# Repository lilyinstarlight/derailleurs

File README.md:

The Derailleurs
===============

The Derailleurs aim to create a system for automatic rear gear switching on a standard bicycle. This repository contains everything we've made toward that goal.

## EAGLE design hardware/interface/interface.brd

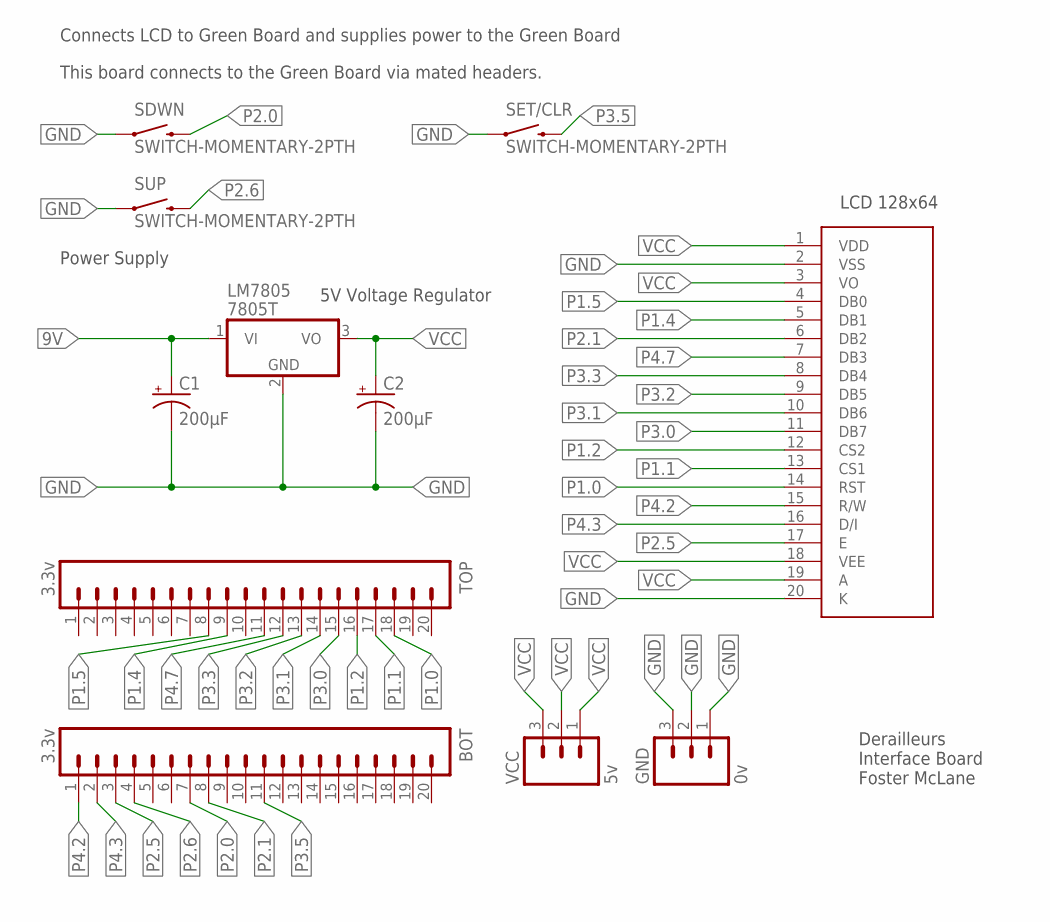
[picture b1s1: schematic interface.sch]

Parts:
BOT: 3.3v; 1X20
C1, C2: 200µF; CPOL-RADIAL-100UF-25V
GND: 0v; 1X03
LM7805: 7805T; TO220H
SDWN: SWITCH-MOMENTARY-2PTH; TACTILE-PTH
SET/CLR: SWITCH-MOMENTARY-2PTH; TACTILE-PTH
SUP: SWITCH-MOMENTARY-2PTH; TACTILE-PTH
TOP: 3.3v; 1X20
U$1: LCD-G12864FULL; LCD-G12864
VCC: 5v; 1X03

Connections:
9V: C1.1 (+), LM7805.1 (VI)
GND: C1.2 (-), C2.2 (-), GND.1, GND.2, GND.3, LM7805.2 (GND), SDWN.1, SET/CLR.1, SUP.1, U$1.2 (VSS), U$1.20 (K)
P1.0: TOP.18, U$1.14 (RST)
P1.1: TOP.17, U$1.13 (CS1)
P1.2: TOP.16, U$1.12 (CS2)
P1.4: TOP.9, U$1.5 (DB1)
P1.5: TOP.8, U$1.4 (DB0)
P2.0: BOT.7, SDWN.3 (2)
P2.1: BOT.8, U$1.6 (DB2)
P2.5: BOT.3, U$1.17 (E)
P2.6: BOT.4, SUP.3 (2)
P3.0: TOP.15, U$1.11 (DB7)
P3.1: TOP.14, U$1.10 (DB6)
P3.2: TOP.13, U$1.9 (DB5)
P3.3: TOP.12, U$1.8 (DB4)
P3.5: BOT.11, SET/CLR.3 (2)
P4.2: BOT.1, U$1.15 (R/W)
P4.3: BOT.2, U$1.16 (D/I)
P4.7: TOP.11, U$1.7 (DB3)
VCC: C2.1 (+), LM7805.3 (VO), U$1.1 (VDD), U$1.3 (VO), U$1.18 (VEE), U$1.19 (A), VCC.1, VCC.2, VCC.3

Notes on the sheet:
LCD 128x64
5V Voltage Regulator
Power Supply
Connects LCD to Green Board and supplies power to the Green Board
This board connects to the Green Board via mated headers.
Derailleurs Interface Board Foster McLane

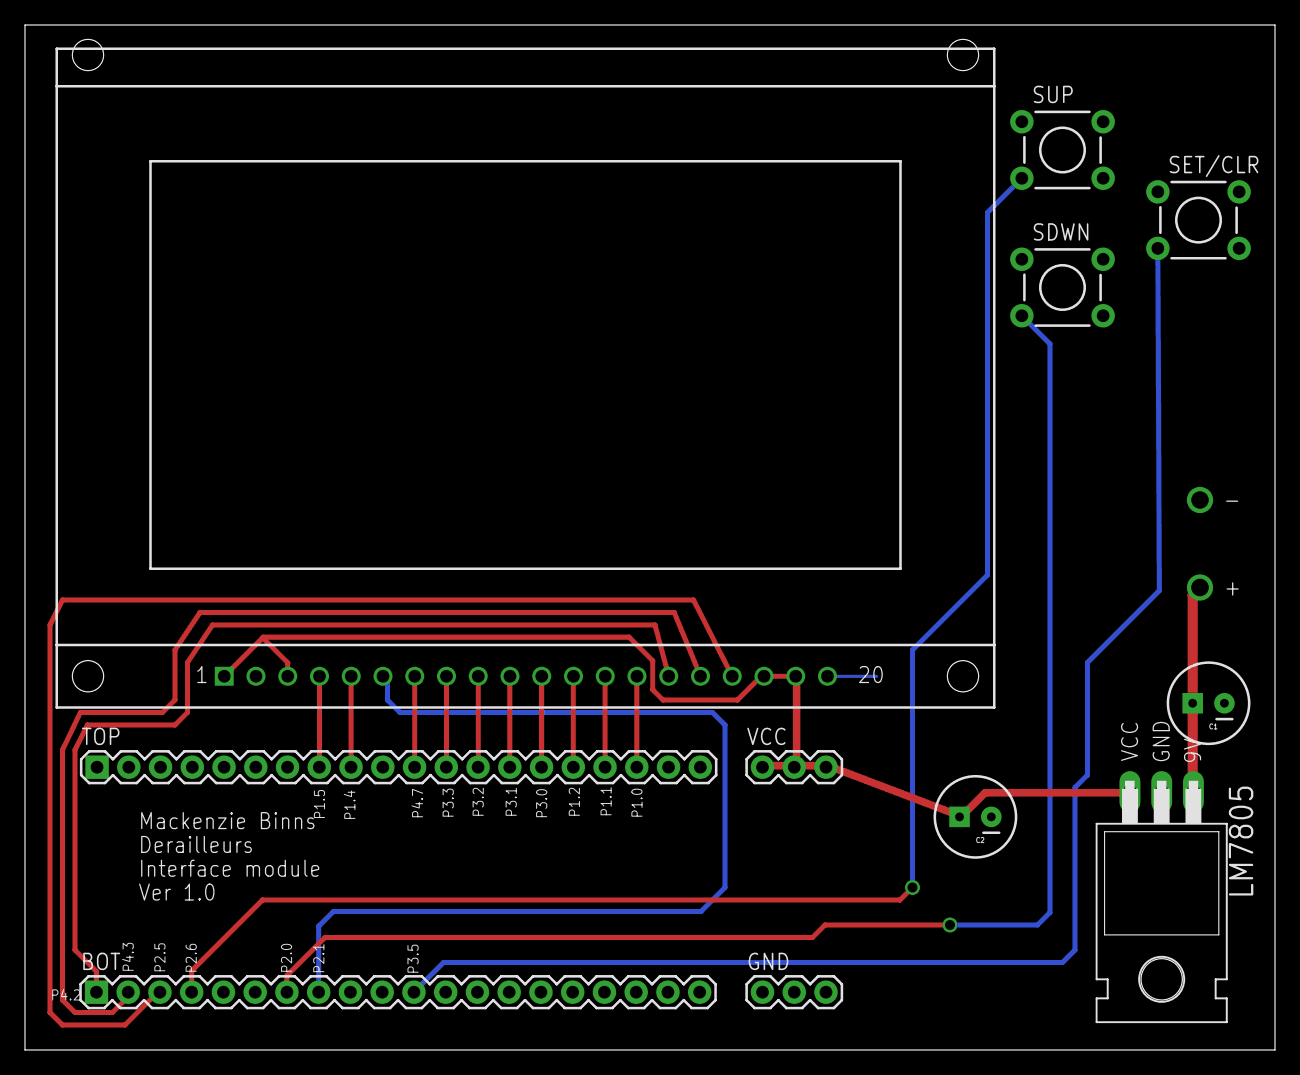
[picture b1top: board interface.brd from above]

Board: 2 copper layers, 100.0 x 82.0 mm, 11 parts (0 on the bottom side), 20 nets.

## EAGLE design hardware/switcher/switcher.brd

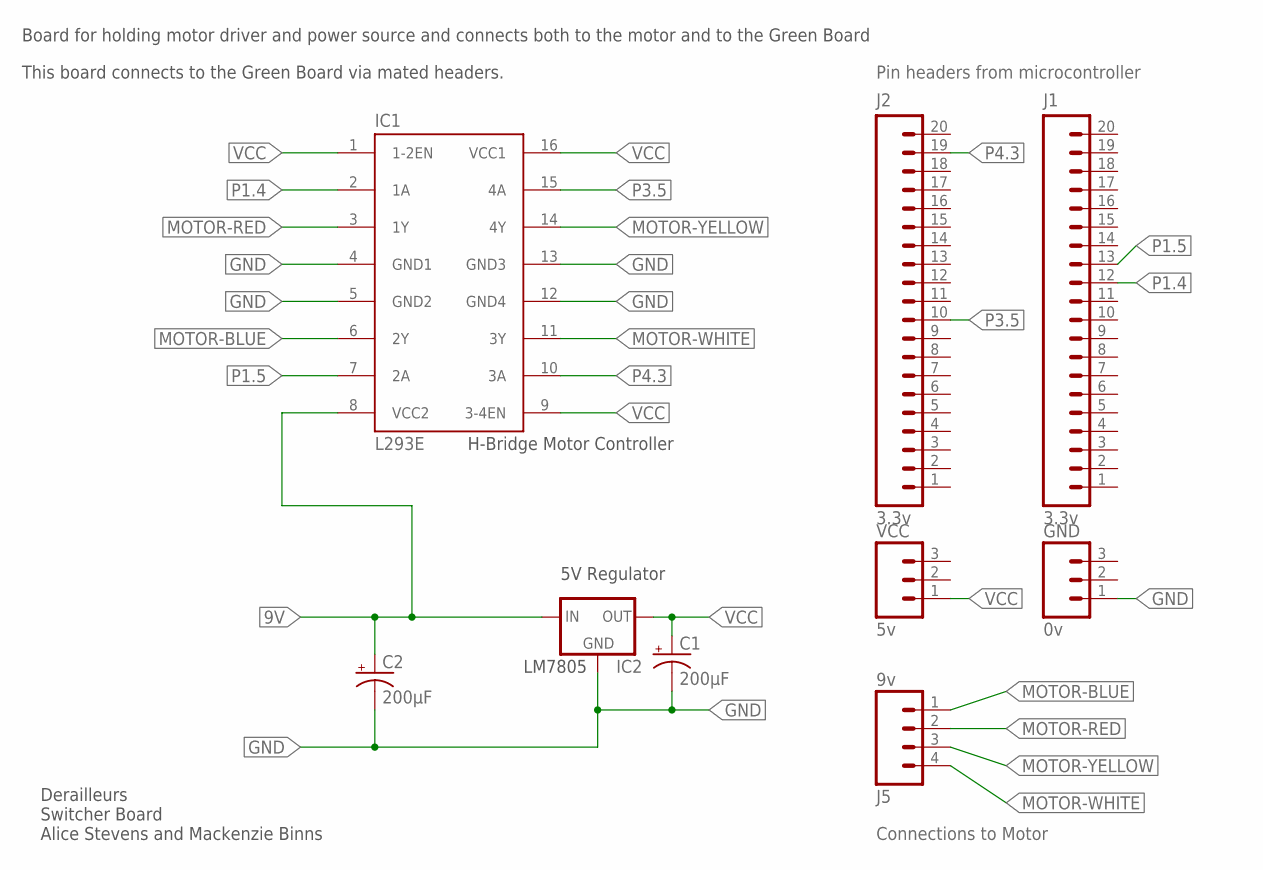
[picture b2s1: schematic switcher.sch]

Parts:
C1, C2: 200µF; CPOL-RADIAL-100UF-25V
GND: 0v; 1X03
IC1: L293E; DIL16
IC2: 78XXL
J1, J2: 3.3v; 1X20
J5: 9v; 1X04
VCC: 5v; 1X03

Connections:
9V: C2.1 (+), IC1.8 (VCC2), IC2.IN
GND: C1.2 (-), C2.2 (-), GND.1, IC1.4 (GND1), IC1.5 (GND2), IC1.12 (GND4), IC1.13 (GND3), IC2.GND
MOTOR-BLUE: IC1.6 (2Y), J5.1
MOTOR-RED: IC1.3 (1Y), J5.2
MOTOR-WHITE: IC1.11 (3Y), J5.4
MOTOR-YELLOW: IC1.14 (4Y), J5.3
P1.4: IC1.2 (1A), J1.12
P1.5: IC1.7 (2A), J1.13
P3.5: IC1.15 (4A), J2.10
P4.3: IC1.10 (3A), J2.19
VCC: C1.1 (+), IC1.1 (1-2EN), IC1.9 (3-4EN), IC1.16 (VCC1), IC2.OUT, VCC.1

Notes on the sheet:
Board for holding motor driver and power source and connects both to the motor and to the Green Board
H-Bridge Motor Controller
LM7805
5V Regulator
This board connects to the Green Board via mated headers.
Derailleurs Switcher Board Alice Stevens and Mackenzie Binns
Pin headers from microcontroller
Connections to Motor

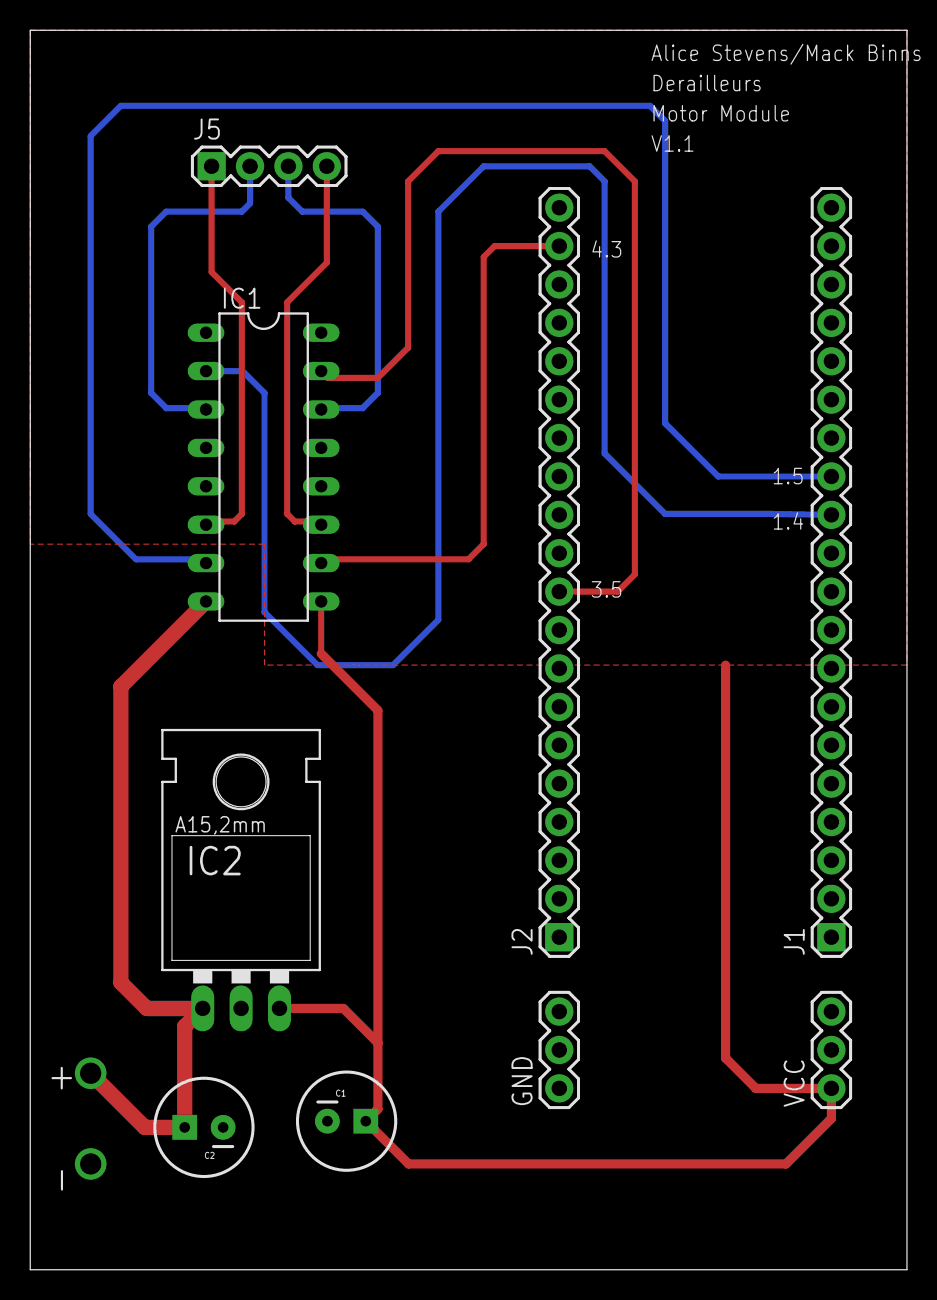
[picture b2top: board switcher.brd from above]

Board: 2 copper layers, 58.0 x 82.0 mm, 9 parts (0 on the bottom side), 11 nets.

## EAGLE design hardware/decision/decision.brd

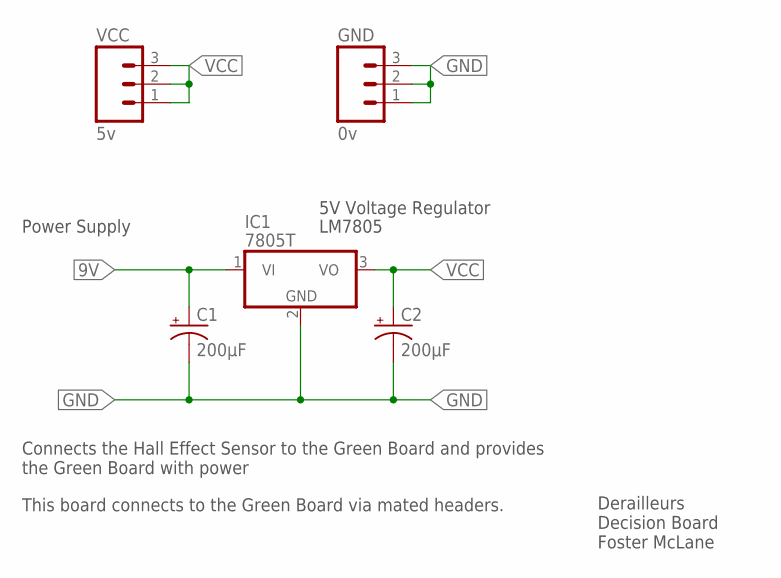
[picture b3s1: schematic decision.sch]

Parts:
C1, C2: 200µF; CPOL-RADIAL-100UF-25V
GND: 0v; 1X03
IC1: 7805T; TO220H
VCC: 5v; 1X03

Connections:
9V: C1.1 (+), IC1.1 (VI)
GND: C1.2 (-), C2.2 (-), GND.1, GND.2, GND.3, IC1.2 (GND)
VCC: C2.1 (+), IC1.3 (VO), VCC.1, VCC.2, VCC.3

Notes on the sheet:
LM7805
5V Voltage Regulator
Connects the Hall Effect Sensor to the Green Board and provides the Green Board with power
This board connects to the Green Board via mated headers.
Derailleurs Decision Board Foster McLane
Power Supply

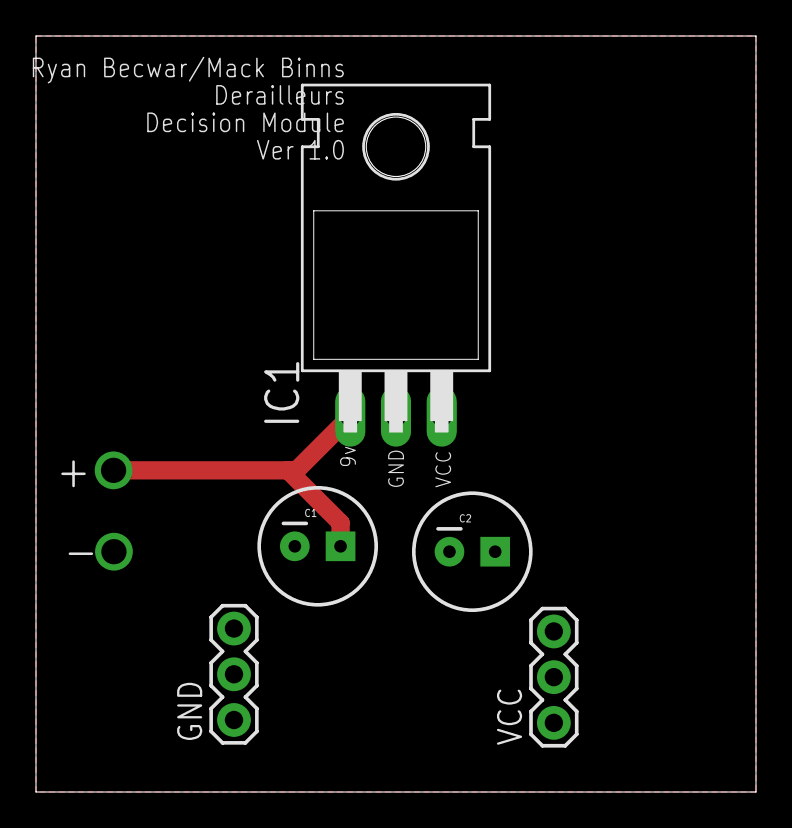
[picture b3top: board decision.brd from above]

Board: 2 copper layers, 40.0 x 42.0 mm, 5 parts (0 on the bottom side), 3 nets.

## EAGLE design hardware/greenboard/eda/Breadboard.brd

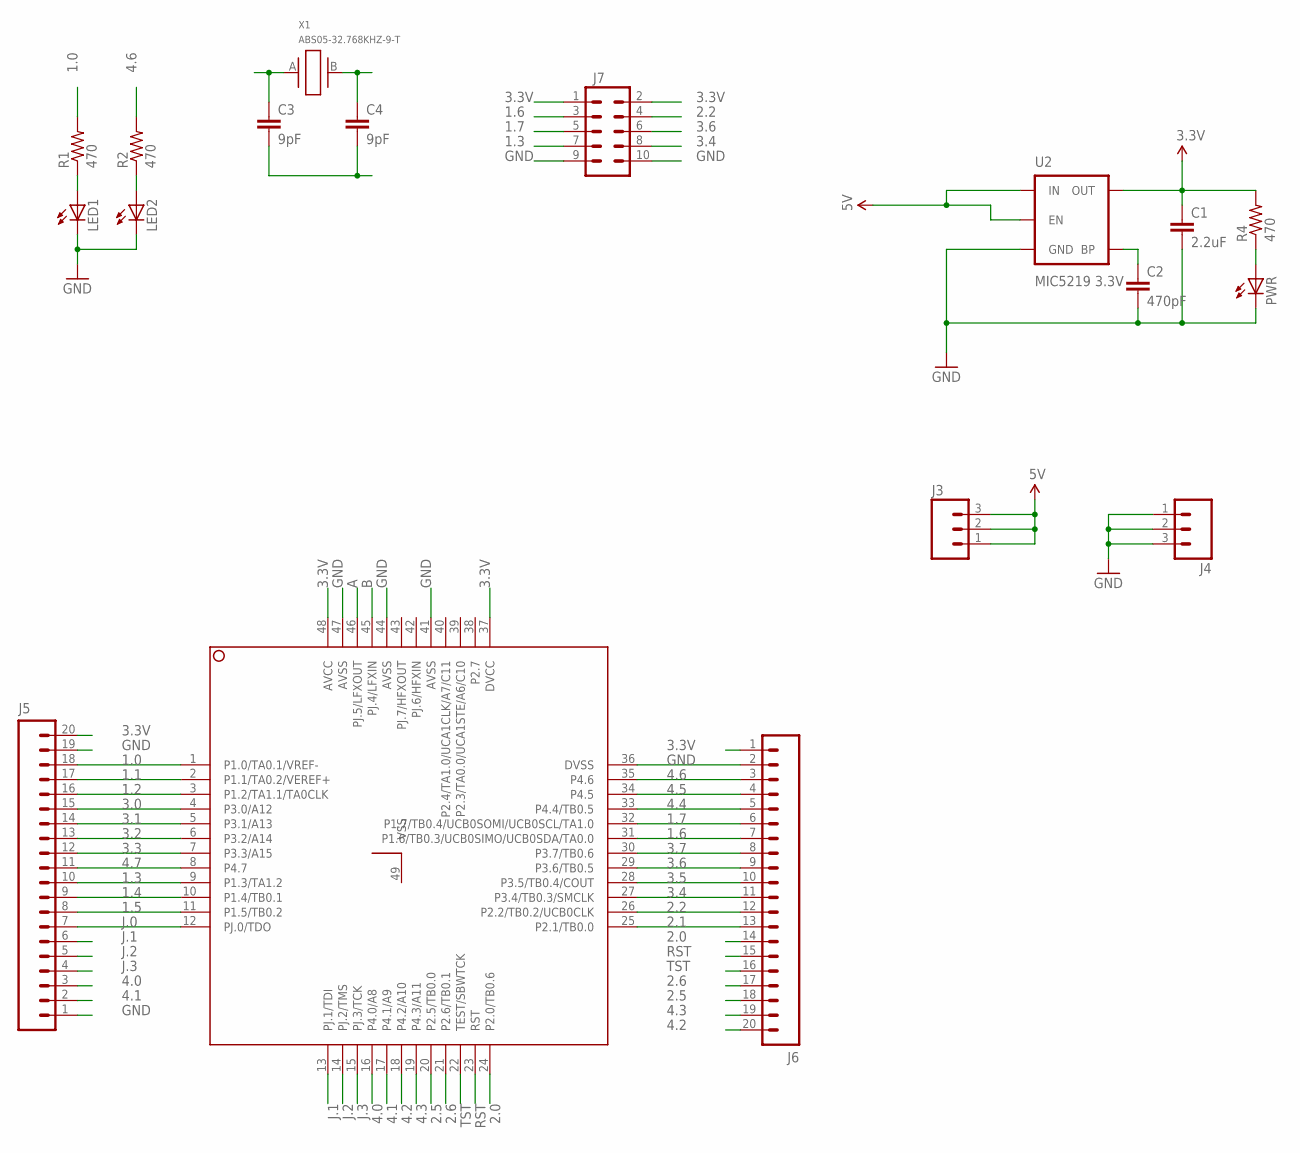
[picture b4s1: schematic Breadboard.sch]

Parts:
C1: 2.2uF; 0603-CAP
C2: 470pF; 0603-CAP
C3, C4: 9pF; 0603-CAP
J3, J4: M031X03_NO_SILK; 1X03_NO_SILK
J5, J6: M20NOSILK; 1X20_NOSILK
J7: M05X2NO_SILK; 2X5_NOSILK
LED1, LED2: LEDCHIPLED_0805; CHIPLED_0805
PWR: LEDCHIPLED_0805; CHIPLED_0805
R1, R2, R4: 470; 0805
U1: MSP430FR5969_RGZ_48; RGZ48_4P1X4P1
U2: MIC5219 3.3V; SOT23-5
X1: ABS05-32.768KHZ-9-T; ABS05

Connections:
1.0: J5.18, R1.2, U1.1 (P1.0/TA0.1/VREF-)
1.1: J5.17, U1.2 (P1.1/TA0.2/VEREF+)
1.2: J5.16, U1.3 (P1.2/TA1.1/TA0CLK)
1.3: J5.10, J7.7, U1.9 (P1.3/TA1.2)
1.4: J5.9, U1.10 (P1.4/TB0.1)
1.5: J5.8, U1.11 (P1.5/TB0.2)
1.6: J6.7, J7.3, U1.31 (P1.6/TB0.3/UCB0SIMO/UCB0SDA/TA0.0)
1.7: J6.6, J7.5, U1.32 (P1.7/TB0.4/UCB0SOMI/UCB0SCL/TA1.0)
2.0: J6.14, U1.24 (P2.0/TB0.6)
2.1: J6.13, U1.25 (P2.1/TB0.0)
2.2: J6.12, J7.4, U1.26 (P2.2/TB0.2/UCB0CLK)
2.5: J6.18, U1.20 (P2.5/TB0.0)
2.6: J6.17, U1.21 (P2.6/TB0.1)
3.0: J5.15, U1.4 (P3.0/A12)
3.1: J5.14, U1.5 (P3.1/A13)
3.2: J5.13, U1.6 (P3.2/A14)
3.3: J5.12, U1.7 (P3.3/A15)
3.3V: C1.1, J5.20, J6.1, J7.1, J7.2, R4.2, U1.37 (DVCC), U1.48 (AVCC), U2.5 (OUT)
3.4: J6.11, J7.8, U1.27 (P3.4/TB0.3/SMCLK)
3.5: J6.10, U1.28 (P3.5/TB0.4/COUT)
3.6: J6.9, J7.6, U1.29 (P3.6/TB0.5)
3.7: J6.8, U1.30 (P3.7/TB0.6)
4.0: J5.3, U1.16 (P4.0/A8)
4.1: J5.2, U1.17 (P4.1/A9)
4.2: J6.20, U1.18 (P4.2/A10)
4.3: J6.19, U1.19 (P4.3/A11)
4.4: J6.5, U1.33 (P4.4/TB0.5)
4.5: J6.4, U1.34 (P4.5)
4.6: J6.3, R2.2, U1.35 (P4.6)
4.7: J5.11, U1.8 (P4.7)
5V: J3.1, J3.2, J3.3, U2.1 (IN), U2.3 (EN)
A: C3.1, U1.46 (PJ.5/LFXOUT), X1.A (1)
B: C4.1, U1.45 (PJ.4/LFXIN), X1.B (2)
GND: C1.2, C2.2, C3.2, C4.2, J4.1, J4.2, J4.3, J5.1, J5.19, J6.2, J7.9, J7.10, LED1.C, LED2.C, PWR.C, U1.36 (DVSS), U1.41 (AVSS), U1.44 (AVSS), U1.47 (AVSS), U2.2 (GND)
J.0: J5.7, U1.12 (PJ.0/TDO)
J.1: J5.6, U1.13 (PJ.1/TDI)
J.2: J5.5, U1.14 (PJ.2/TMS)
J.3: J5.4, U1.15 (PJ.3/TCK)
unnamed: LED2.A, R2.1
unnamed: PWR.A, R4.1
unnamed: LED1.A, R1.1
unnamed: C2.1, U2.4 (BP)
RST: J6.15, U1.23 (RST)
TST: J6.16, U1.22 (TEST/SBWTCK)

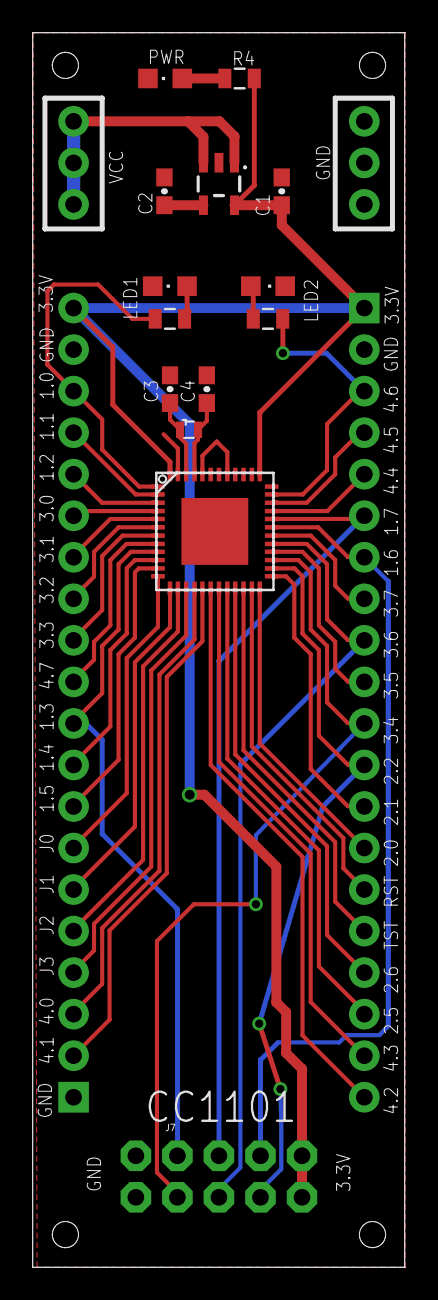
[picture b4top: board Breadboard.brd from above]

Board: 2 copper layers, 22.8 x 75.5 mm, 18 parts (0 on the bottom side), 44 nets.

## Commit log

2016-09-02 add initial files an energia makefile
2016-09-02 add a gitignore
2016-09-02 add MyBlink example to test programming setup
2016-09-04 update energia makefile
2016-09-04 add non-working Send and Recv programs
2016-09-04 rename MyBlink to FibBlink
2016-09-07 add cc1101 library
2016-09-07 update makefile
2016-09-07 update gitignore
2016-09-07 remove non-working Recv and Send and import working RX and TX
2016-09-07 add makefile directory as sketchbook
2016-09-07 update makefile to avoid environment variables
2016-09-08 rewrite TX and RX to send strings
2016-09-09 fix string transmission
2016-09-10 add more updates to RX/TX example code
2016-09-14 add working transmit
2016-09-22 add MySerial library for our 2-wire serial implementation
2016-09-22 add tester program for serial implementation
2016-09-22 update library for any pins
2016-09-26 Reorgainized git repository to something more sane
2016-09-26 Merging changes from foster
2016-09-26 Fixing misspelling on directory
2016-09-26 reorganize repository a bit
2016-09-26 add schematic for the interface board
2016-09-26 Adding motor schematic
2016-09-26 Moving MotorChip.sch to hardware interfaces
2016-09-26 organize motorchip.sch into switch.sch
2016-09-26 move docs to documents
2016-09-26 fix Ryan's name
2016-09-26 Adding second gitrepo to documentation
2016-09-26 Clearing up what repo is live and what is mirror
2016-09-26 update schematics
2016-09-30 add Lock program
2016-09-30 remove blink_state from Lock
2016-09-30 update Lock to include latest features
2016-09-30 add capacitors
2016-09-30 handle last max_code digit
2016-10-03 add decision board file
2016-10-03 update decision board with proper nets
2016-10-03 working on decision board traces
2016-10-03 Add interface.brd, it may need a copper pour
2016-10-03 Add switcher.brd to repo, May need cleanup
2016-10-03 update decision board with copper pools, silk screen, and proper routes
2016-10-03 update interface schematic
2016-10-03 finish boards
2016-10-03 added test plan
2016-10-04 Finish routing all boards, schematics are consitant, and all deliverable requirements are met..
2016-10-04 Update TestPlan.pdf with team information and changed formatting
2016-10-04 Fix spelling mistake in derailleurs on silk screen
2016-10-04 Meeting Deliverable requirements by adding git repo's
2016-11-01 testing sensor board
2016-11-01 Preliminary Hall Effect sensor code
2016-11-01 Test for motor using enable pins and buttons operation.
2016-11-01 Test for photoresistor on sensor board made in class.
2016-11-01 Test for accelerometer on sensorboard.
2016-11-02 adding model for motor mounting bracket
2016-11-02 Update gitignore to not track DS_Store files
2016-11-02 Update hallsensor code to reflect changes in wiring on breadboard using pullup resistor
2016-11-02 Moved ADXL362 simple read
2016-11-03 Update motor mount model with slot for wires.
2016-11-03 fix moving average
2016-11-04 Got lcd driver working with MSP430
2016-11-04 tinkering with contrast to make display readable
2016-11-04 Add comments to rpm_module to describe code functionality, renamed hall_test to rpm_modle for clarity in deliverable 5
2016-11-04 Interface now displays target and current cadence, increments and decrements w buttons
2016-11-04 Toying with the RPM calculator, only returns 15 rpm increments, added a test folder for unit tests
2016-11-04 tracking rpm_module
2016-11-04 Finished random number average unit test for cal_average, updated rpm_module to have correct percision, working on shifting logic
2016-11-04 restructuring
2016-11-04 Adding gear shifting code and unit test
2016-11-04 finishing up shifting logic unit test, integrating shifting logic skeleton into rpm_module code
2016-11-04 Adding text file for unit tests
2016-11-04 Fixing typos in motor unit tests
2016-11-04 Polishng up rpm_module for deliverable 5
2016-11-04 Added unit tests and current gear display
2016-11-04 Updated test docuement to reflect new unit tests
2016-11-04 Cleaning repo for deliverable 5, update testing.txt to spec, fixed warning messages in rpm_module and tests_modules
2016-11-04 Adding current motor module code and updating test code
2016-11-07 Added program to move motor and report change in step to tune gear change
2016-11-07 Updating motor programs with tuned gear change value
2016-11-07 add a deliverables directory to the gitignore
2016-11-07 Clean lcdController.ino file up and moved function out into .h file contained in libraries folder
2016-11-07 Adding turnbuckle clamp model and stl
2016-11-08 Trying to get comms working with LCD controller
2016-11-08 make RX and TX work
2016-11-08 add skeleton folders for software
2016-11-08 add decision and switcher files with working radio
2016-11-08 fix small compilation errors
2016-11-08 fix small logic error
2016-11-09 remove question
2016-11-09 update switcher
2016-11-09 fix the gear numbering
2016-11-09 Adding stls for sensor mount
2016-11-15 add minimum shifting cadence logic
2016-11-16 add code necessary to add to interface program for radio
2016-11-17 add ADXL362 library
2016-11-17 add pedometer
2016-11-18 add comments and fix shifting
2016-12-11 add constants.h file

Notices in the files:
parts and their libraries:
SparkFun-Capacitors: Licensing: Creative Commons ShareAlike 4.0 International - https://creativecommons.org/licenses/by-sa/4.0
